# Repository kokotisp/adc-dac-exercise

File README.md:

# adc-dac-exercise
Σκοπος της παρουσας εργασιας ειναι ο σχεδιασμος και η κατασκευη μιας καρτας 
επεκτασης ADC-DAC για το raspberry pi που θα επιτρεπει την ληψη αναλογικων 
μετρησεων και την εξοδο σηματος ηχου.

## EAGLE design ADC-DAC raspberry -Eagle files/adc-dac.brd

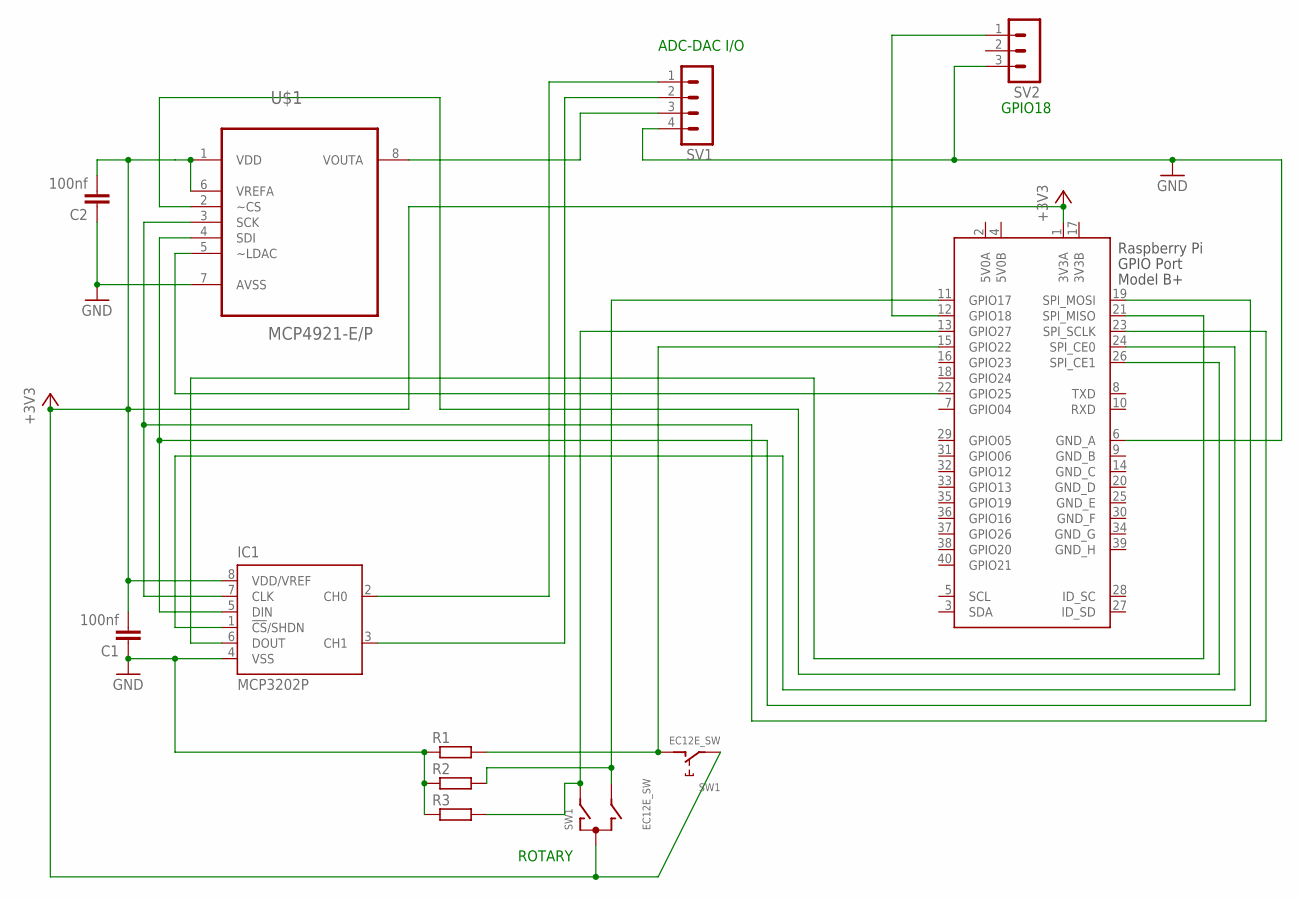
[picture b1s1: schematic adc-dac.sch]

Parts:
C1, C2: 100nf; C1210
IC1: MCP3202P; DIL8
R1, R2, R3: R-EU_0204/2V; 0204V
SV1: MA04-1
SV2: MA03-1
SW1: EC12E_SW; ALPS_EC12E_SW
U$1: MCP4921-E/P; DIP254P762X432-8
X1: RASPI_BOARD_B+#_H; RASPI_BOARD_B+HAT

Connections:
3V3B: X1.17 (3V3B)
5V0A: X1.2 (5V0A)
5V0B: X1.4 (5V0B)
+3V3: C1.2, C2.2, IC1.8 (VDD/VREF), SW1.C, SW1.E (2), U$1.1 (VDD), U$1.6 (VREFA), X1.1 (3V3A)
GND: C1.1, C2.1, IC1.4 (VSS), R1.1, R2.1, R3.1, SV1.4, SV2.3, U$1.7 (AVSS), X1.6 (GND_A)
GND_B: X1.9 (GND_B)
GND_C: X1.14 (GND_C)
GND_D: X1.20 (GND_D)
GND_E: X1.25 (GND_E)
GND_F: X1.30 (GND_F)
GND_G: X1.34 (GND_G)
GND_H: X1.39 (GND_H)
unnamed: IC1.2 (CH0), SV1.1
unnamed: IC1.3 (CH1), SV1.2
unnamed: SV1.3, U$1.8 (VOUTA)
unnamed: IC1.7 (CLK), U$1.3 (SCK), X1.23 (SPI_SCLK)
unnamed: IC1.5 (DIN), U$1.4 (SDI), X1.19 (SPI_MOSI)
unnamed: U$1.5 (~LDAC), X1.22 (GPIO25)
unnamed: IC1.1 (!CS!/SHDN), X1.24 (SPI_CE0)
unnamed: U$1.2 (~CS), X1.26 (SPI_CE1)
unnamed: IC1.6 (DOUT), X1.21 (SPI_MISO)
unnamed: R1.2, SW1.D (1), X1.15 (GPIO22)
unnamed: R3.2, SW1.A, X1.13 (GPIO27)
unnamed: R2.2, SW1.B, X1.11 (GPIO17)
unnamed: SV2.1, X1.12 (GPIO18)

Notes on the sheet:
ADC-DAC I/O
GPIO18
ROTARY

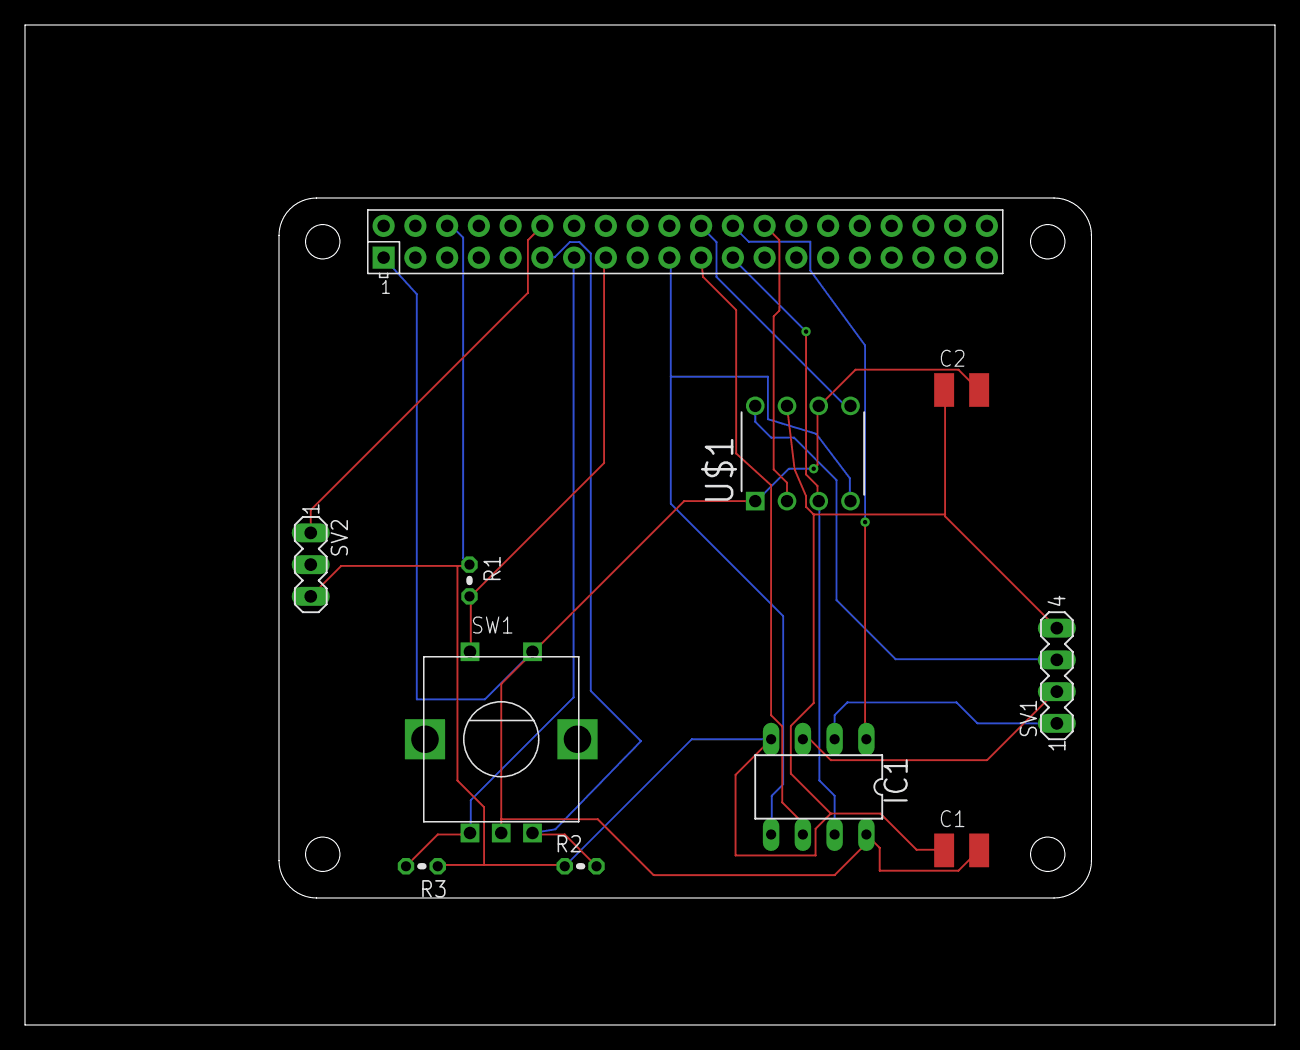
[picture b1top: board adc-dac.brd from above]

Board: 2 copper layers, 100.0 x 80.0 mm, 11 parts (0 on the bottom side), 15 nets.
